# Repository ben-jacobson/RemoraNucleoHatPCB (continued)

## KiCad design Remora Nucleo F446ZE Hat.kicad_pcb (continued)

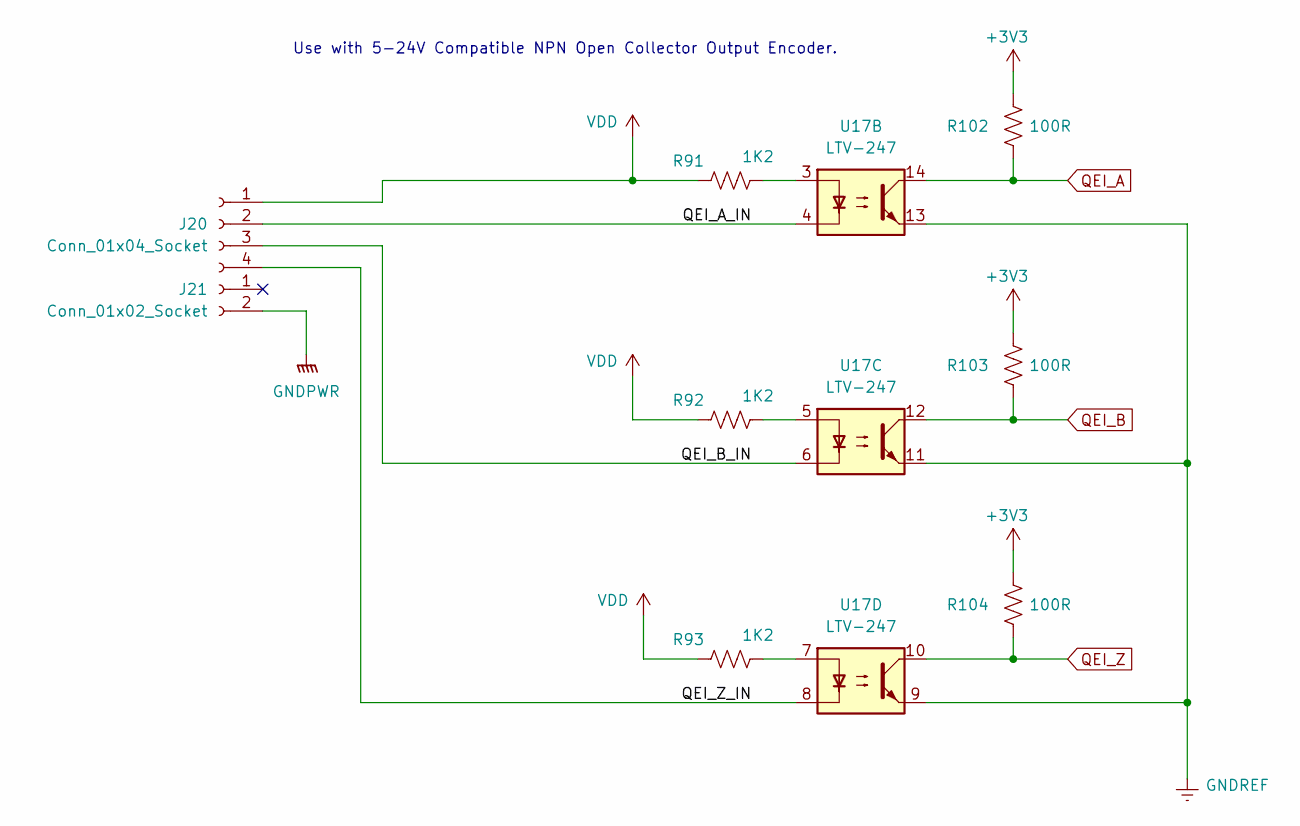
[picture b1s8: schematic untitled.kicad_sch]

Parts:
J20: Conn_01x04_Socket; 691412120004B; Digikey Part Number 732-691412120004B-ND
J21: Conn_01x02_Socket; 691412120002B; Digikey Part Number 732-691412120002B-ND
R91, R92, R93: 1K2; R_1206_3216Metric_Pad1.30x1.75mm_HandSolder; Digikey Part Number RMCF1206JT1K20CT-ND
R102, R103, R104: 100R; R_1206_3216Metric_Pad1.30x1.75mm_HandSolder
U17: LTV-247; SOP-16_4.4x10.4mm_P1.27mm; Digikey Part Number 160-2255-1-ND

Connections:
+3V3: R102.1, R103.1, R104.1; also elsewhere on the board
/Encoder Inputs/QEI_A_IN: J20.2, U17.4
/Encoder Inputs/QEI_B_IN: J20.3, U17.6
/Encoder Inputs/QEI_Z_IN: J20.4, U17.8
GNDPWR: J21.2; also elsewhere on the board
GNDREF: U17.9, U17.11, U17.13; also elsewhere on the board
unnamed: R91.1, U17.3
unnamed: R92.1, U17.5
unnamed: R93.1, U17.7
QEI_A: R102.2, U17.14; also elsewhere on the board
QEI_B: R103.2, U17.12; also elsewhere on the board
QEI_Z: R104.2, U17.10; also elsewhere on the board
VDD: J20.1, R91.2, R92.2, R93.2; also elsewhere on the board

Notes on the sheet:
Use with 5-24V Compatible NPN Open Collector Output Encoder.

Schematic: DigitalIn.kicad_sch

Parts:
R33, R34, R35, R36: 180R; R_1206_3216Metric_Pad1.30x1.75mm_HandSolder; Digikey Part Number 311-180FRCT-ND
U7: LTV-247; SOP-16_4.4x10.4mm_P1.27mm; Digikey Part Number 160-2255-1-ND

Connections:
+5VD: R33.1, R34.1, R35.1, R36.1; also elsewhere on the board
/Digital Inputs/Digital Input 4-7/INPUT4: U7.2; also elsewhere on the board
/Digital Inputs/Digital Input 4-7/INPUT5: U7.4; also elsewhere on the board
/Digital Inputs/Digital Input 4-7/INPUT6: U7.6; also elsewhere on the board
/Digital Inputs/Digital Input 4-7/INPUT7: U7.8; also elsewhere on the board
GNDREF: U7.9, U7.11, U7.13, U7.15; also elsewhere on the board
MCU_DIGITAL_IN_4: U7.16; also elsewhere on the board
MCU_DIGITAL_IN_5: U7.14; also elsewhere on the board
MCU_DIGITAL_IN_6: U7.12; also elsewhere on the board
MCU_DIGITAL_IN_7: U7.10; also elsewhere on the board
unnamed: R33.2, U7.1
unnamed: R34.2, U7.3
unnamed: R35.2, U7.5
unnamed: R36.2, U7.7

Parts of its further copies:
R41, R42, R43, R44, R45, R46, R47, R48, R49, R50, R51, R52: 180R; R_1206_3216Metric_Pad1.30x1.75mm_HandSolder; Digikey Part Number 311-180FRCT-ND
U9, U10, U11: LTV-247; SOP-16_4.4x10.4mm_P1.27mm; Digikey Part Number 160-2255-1-ND

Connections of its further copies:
+5VD: R41.1, R42.1, R43.1, R44.1, R45.1, R46.1, R47.1, R48.1, R49.1, R50.1, R51.1, R52.1; also elsewhere on the board
/Digital Inputs/Digital Input 0-3/INPUT0: U11.2; also elsewhere on the board
/Digital Inputs/Digital Input 0-3/INPUT1: U11.4; also elsewhere on the board
/Digital Inputs/Digital Input 0-3/INPUT2: U11.6; also elsewhere on the board
/Digital Inputs/Digital Input 0-3/INPUT3: U11.8; also elsewhere on the board
/Digital Inputs/Digital Input 8-11/INPUT8: U9.2; also elsewhere on the board
/Digital Inputs/Digital Input 8-11/INPUT9: U9.4; also elsewhere on the board
/Digital Inputs/Digital Input 8-11/INPUT10: U9.6; also elsewhere on the board
/Digital Inputs/Digital Input 8-11/INPUT11: U9.8; also elsewhere on the board
/Digital Inputs/Digital Input 12-15/INPUT12: U10.2; also elsewhere on the board
/Digital Inputs/Digital Input 12-15/INPUT13: U10.4; also elsewhere on the board
/Digital Inputs/Digital Input 12-15/INPUT14: U10.6; also elsewhere on the board
/Digital Inputs/Digital Input 12-15/INPUT15: U10.8; also elsewhere on the board
GNDREF: U9.9, U9.11, U9.13, U9.15, U10.9, U10.11, U10.13, U10.15, U11.9, U11.11, U11.13, U11.15; also elsewhere on the board
MCU_DIGITAL_IN_0: U11.16; also elsewhere on the board
MCU_DIGITAL_IN_1: U11.14; also elsewhere on the board
MCU_DIGITAL_IN_2: U11.12; also elsewhere on the board
MCU_DIGITAL_IN_3: U11.10; also elsewhere on the board
MCU_DIGITAL_IN_8: U9.16; also elsewhere on the board
MCU_DIGITAL_IN_9: U9.14; also elsewhere on the board
MCU_DIGITAL_IN_10: U9.12; also elsewhere on the board
MCU_DIGITAL_IN_11: U9.10; also elsewhere on the board
MCU_DIGITAL_IN_12: U10.16; also elsewhere on the board
MCU_DIGITAL_IN_13: U10.14; also elsewhere on the board
MCU_DIGITAL_IN_14: U10.12; also elsewhere on the board
MCU_DIGITAL_IN_15: U10.10; also elsewhere on the board
unnamed: R41.2, U9.1
unnamed: R42.2, U9.3
unnamed: R43.2, U9.5
unnamed: R44.2, U9.7
unnamed: R45.2, U10.1
unnamed: R46.2, U10.3
unnamed: R47.2, U10.5
unnamed: R48.2, U10.7
unnamed: R49.2, U11.1
unnamed: R50.2, U11.3
unnamed: R51.2, U11.5
unnamed: R52.2, U11.7

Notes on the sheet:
NPN Inputs

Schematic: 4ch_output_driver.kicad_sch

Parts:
F1, F2, F3, F4: PRG18BB330MB1RB; Fuse_0603_1608Metric_Pad1.05x0.95mm_HandSolder; Digikey Part Number 490-2471-1-ND
R29, R30, R31, R32: 180R; R_1206_3216Metric_Pad1.30x1.75mm_HandSolder; Digikey Part Number 311-180FRCT-ND
U6: LTV-247; SOP-16_4.4x10.4mm_P1.27mm; Digikey Part Number 160-2255-1-ND

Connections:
/Digital Outputs/4CH digital output driver 1/OUTPUT0: F1.2; also elsewhere on the board
/Digital Outputs/4CH digital output driver 1/OUTPUT1: F2.2; also elsewhere on the board
/Digital Outputs/4CH digital output driver 1/OUTPUT2: F3.2; also elsewhere on the board
/Digital Outputs/4CH digital output driver 1/OUTPUT3: F4.2; also elsewhere on the board
GNDPWR: U6.9, U6.11, U6.13, U6.15; also elsewhere on the board
GNDREF: U6.2, U6.4, U6.6, U6.8; also elsewhere on the board
MCU_DIGITAL_OUT_0: R29.1; also elsewhere on the board
MCU_DIGITAL_OUT_1: R30.1; also elsewhere on the board
MCU_DIGITAL_OUT_2: R31.1; also elsewhere on the board
MCU_DIGITAL_OUT_3: R32.1; also elsewhere on the board
unnamed: F1.1, U6.16
unnamed: F2.1, U6.14
unnamed: F3.1, U6.12
unnamed: F4.1, U6.10
unnamed: R29.2, U6.1
unnamed: R30.2, U6.3
unnamed: R31.2, U6.5
unnamed: R32.2, U6.7

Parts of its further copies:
F5, F6, F7, F8: PRG18BB330MB1RB; Fuse_0603_1608Metric_Pad1.05x0.95mm_HandSolder; Digikey Part Number 490-2471-1-ND
R37, R38, R39, R40: 180R; R_1206_3216Metric_Pad1.30x1.75mm_HandSolder; Digikey Part Number 311-180FRCT-ND
U8: LTV-247; SOP-16_4.4x10.4mm_P1.27mm; Digikey Part Number 160-2255-1-ND

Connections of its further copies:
/Digital Outputs/4CH digital output driver 2/OUTPUT4: F5.2; also elsewhere on the board
/Digital Outputs/4CH digital output driver 2/OUTPUT5: F6.2; also elsewhere on the board
/Digital Outputs/4CH digital output driver 2/OUTPUT6: F7.2; also elsewhere on the board
/Digital Outputs/4CH digital output driver 2/OUTPUT7: F8.2; also elsewhere on the board
GNDPWR: U8.9, U8.11, U8.13, U8.15; also elsewhere on the board
GNDREF: U8.2, U8.4, U8.6, U8.8; also elsewhere on the board
MCU_DIGITAL_OUT_4: R37.1; also elsewhere on the board
MCU_DIGITAL_OUT_5: R38.1; also elsewhere on the board
MCU_DIGITAL_OUT_6: R39.1; also elsewhere on the board
MCU_DIGITAL_OUT_7: R40.1; also elsewhere on the board
unnamed: F5.1, U8.16
unnamed: F6.1, U8.14
unnamed: F7.1, U8.12
unnamed: F8.1, U8.10
unnamed: R37.2, U8.1
unnamed: R38.2, U8.3
unnamed: R39.2, U8.5
unnamed: R40.2, U8.7

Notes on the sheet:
NPN Outputs

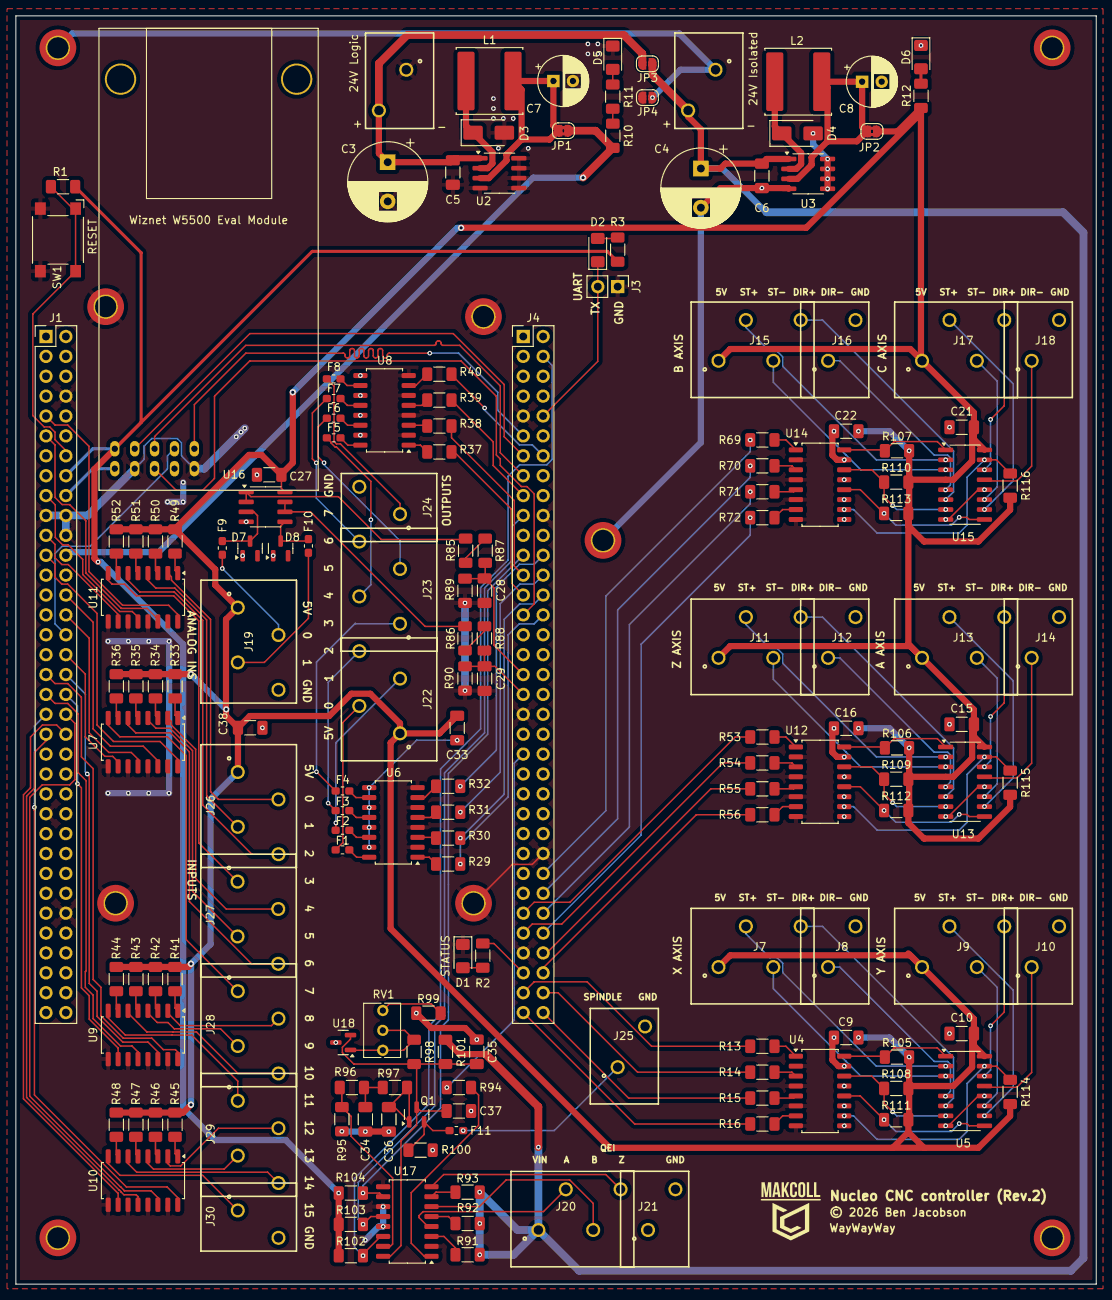
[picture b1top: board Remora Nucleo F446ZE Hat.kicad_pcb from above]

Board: 2 copper layers, 138.0 x 162.0 mm, 179 parts (0 on the bottom side), 194 nets.

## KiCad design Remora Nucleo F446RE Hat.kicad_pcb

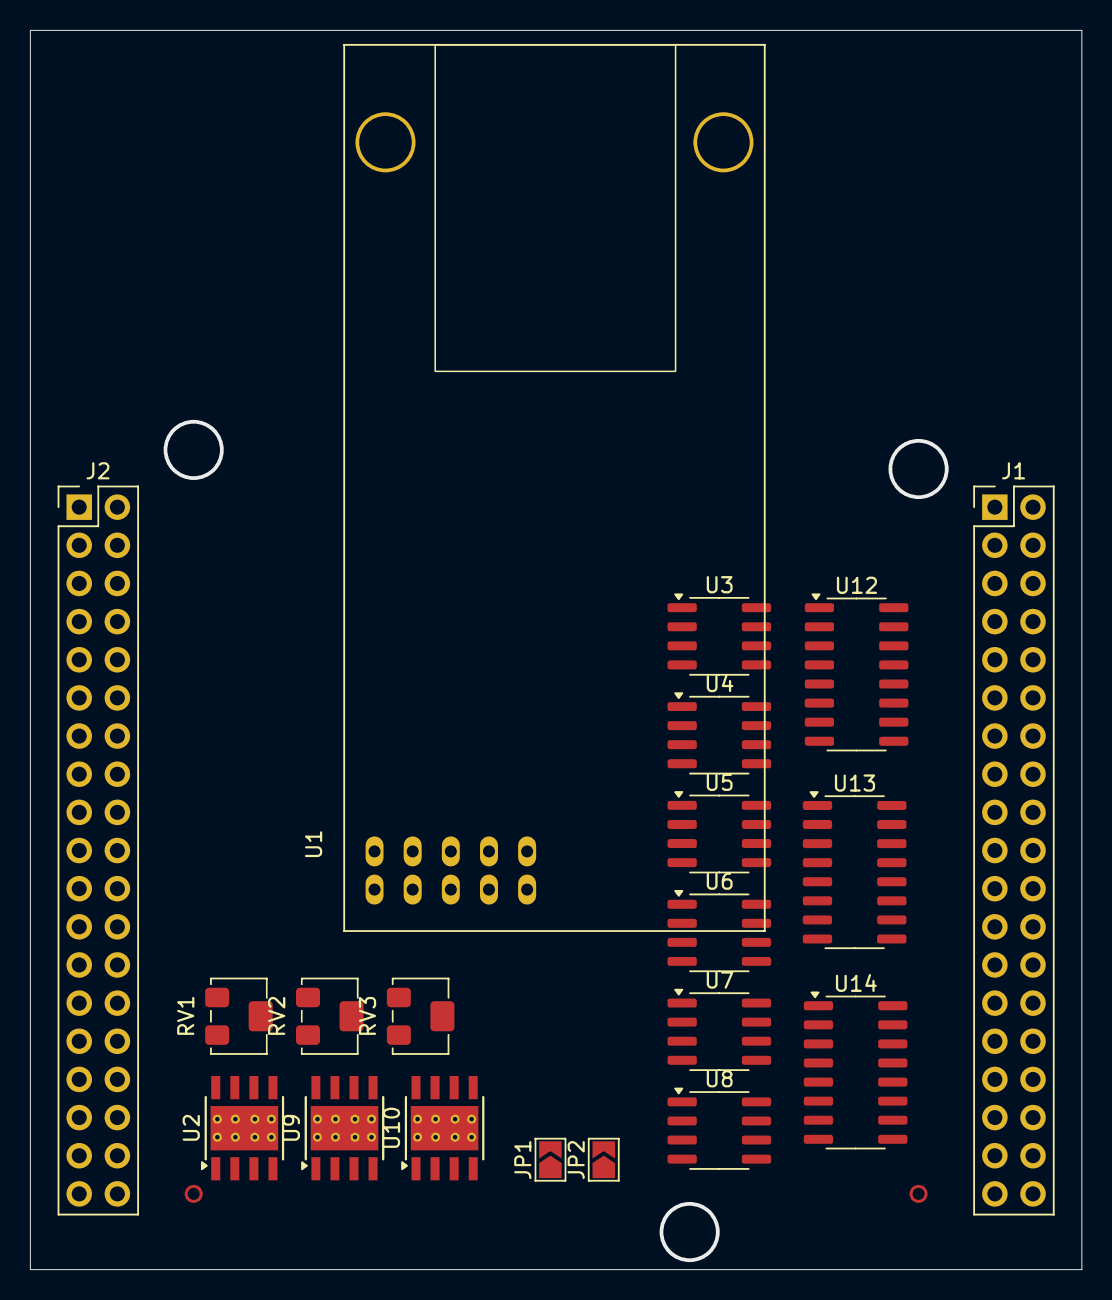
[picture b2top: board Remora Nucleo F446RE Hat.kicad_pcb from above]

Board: 2 copper layers, 70.0 x 82.5 mm, 20 parts (0 on the bottom side), 28 nets, no tracks yet.

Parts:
J1: NucleoF446RE CN10 Header; PinHeader_2x19_P2.54mm_Vertical
J2: NucleoF446RE CN7 Header; PinHeader_2x19_P2.54mm_Vertical
JP1: EXT_5V_SUPPLY_JMP; SolderJumper-2_P1.3mm_Open_TrianglePad1.0x1.5mm
JP2: EXT_5V_GND_JMP; SolderJumper-2_P1.3mm_Open_TrianglePad1.0x1.5mm
RV1, RV3: 50R trimpot; Potentiometer_Bourns_3224W_Vertical
RV2: 500R trimpot; Potentiometer_Bourns_3224W_Vertical
U1: W5500EvalModule
U2, U9, U10: TPS5430DDAR; TI_SO-PowerPAD-8_ThermalVias
U3, U4, U5, U6, U7, U8: ADuM1201AR; SOIC-8_3.9x4.9mm_P1.27mm
U12, U13, U14: HT26LS31ARZ; SOIC-16_3.9x9.9mm_P1.27mm

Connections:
5V_GND: JP2.1 (A), U3.5 (GND2), U4.5 (GND2), U5.5 (GND2), U6.5 (GND2), U7.5 (GND2), U8.5 (GND2), U12.8 (GND), U12.12 (~G), U13.8 (GND), U13.12 (~G), U14.8 (GND), U14.12 (~G)
+3V3: U1.5 (3V3), U3.1 (VDD1), U4.1 (VDD1), U5.1 (VDD1), U6.1 (VDD1), U7.1 (VDD1), U8.1 (VDD1)
+5V: JP1.2 (B), U1.6 (5V)
+5VD: JP1.1 (A), U3.8 (VDD2), U4.8 (VDD2), U5.8 (VDD2), U6.8 (VDD2), U7.8 (VDD2), U8.8 (VDD2), U12.4 (G), U12.16 (VDD), U13.4 (G), U13.16 (VDD), U14.4 (G), U14.16 (VDD)
+12V: U9.7 (VIN), U10.7 (VIN)
GNDREF: J1.9, J1.20, J2.8, J2.19, J2.20, J2.22, JP2.2 (B), U1.7 (GND), U1.10 (GND), U2.6 (GND), U2.9 (GNDPAD), U3.4 (GND1), U4.4 (GND1), U5.4 (GND1), U6.4 (GND1), U7.4 (GND1), U8.4 (GND1), U9.6 (GND), U9.9 (GNDPAD), U10.6 (GND), U10.9 (GNDPAD)
unnamed: RV3.2, RV3.3
unnamed: RV1.2, RV1.3
unnamed: RV2.2, RV2.3
unnamed: U3.2 (VOA), U12.1 (1A)
unnamed: U3.6 (VOB), U12.7 (2A)
unnamed: U4.2 (VOA), U12.9 (3A)
unnamed: U4.6 (VOB), U12.15 (4A)
unnamed: U5.2 (VOA), U13.1 (1A)
unnamed: U5.6 (VOB), U13.7 (2A)
unnamed: U6.2 (VOA), U13.9 (3A)
unnamed: U6.6 (VOB), U13.15 (4A)
unnamed: U7.2 (VOA), U14.1 (1A)
unnamed: U7.6 (VOB), U14.7 (2A)
unnamed: U8.2 (VOA), U14.9 (3A)
unnamed: U8.6 (VOB), U14.15 (4A)
SPI1_CLK: J1.31, U1.1 (SLCK)
SPI1_MISO: J1.27, U1.4 (MISO)
SPI1_MOSI: J1.29, U1.3 (MOSI)
VSENSE: RV1.1, RV2.1, RV3.1, U2.4 (VSENSE), U9.4 (VSENSE), U10.4 (VSENSE)
WIZ_CS: J2.17, U1.2 (SCS)
WIZ_INT: J1.21, U1.9 (INT)
WIZ_RST: J2.37, U1.8 (RST)

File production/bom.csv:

Designator,Footprint,Quantity,Value,LCSC Part #
J1,PinHeader_2x19_P2.54mm_Vertical,1,NucleoF446RE CN10 Header,
J2,PinHeader_2x19_P2.54mm_Vertical,1,NucleoF446RE CN7 Header,
JP1,SolderJumper-2_P1.3mm_Open_TrianglePad1.0x1.5mm,1,EXT_5V_SUPPLY_JMP,
JP2,SolderJumper-2_P1.3mm_Open_TrianglePad1.0x1.5mm,1,EXT_5V_GND_JMP,
"RV1, RV3",Potentiometer_Bourns_3224W_Vertical,2,50R trimpot,
RV2,Potentiometer_Bourns_3224W_Vertical,1,500R trimpot,
U1,W5500EvalModule,1,~,
"U10, U2, U9",TI_SO-PowerPAD-8_ThermalVias,3,TPS5430DDAR,
"U12, U13, U14",SOIC-16_3.9x9.9mm_P1.27mm,3,HT26LS31ARZ,
"U3, U4, U5, U6, U7, U8",SOIC-8_3.9x4.9mm_P1.27mm,6,ADuM1201AR,

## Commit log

2025-06-02 Update README.md
    typo!
2025-06-02 Initial details in README.md
2025-06-02 Modified gitignore for better handling of kicad files
2025-06-02 Initial tidy of untracked files
2025-06-02 missed backups
2025-06-02 more files...
2025-06-02 another unused lock file, that should be it for now
2025-06-04 remapping IO pins around unavailable IO on board. Steppers are still in progress
2025-06-04 Moved UART to use STLink default comms port, frees up 2x GPIO
2025-06-04 Bug no longer reproducible with ZDir. excel mapping is now reflective of what works in software
2025-06-04 updates to some testing, all GPIO and stepper pins now work. Yet to test ABC axis as I don't have any example GCode for it. will have to trust that 5 axis works for now
2025-06-15 Changed board spec from Nucleo F446RE to F446ZE Altered readme to suit it and moved the Todos over.
2025-06-15 Put in disclaimer in README and removed deprecated production file
2025-06-15 tweaked board edge cuts, mouting hole positions and pin headers to match mechanical drawing. Yet to validate with physical hardware
2025-06-16 rewired the UART to use virtual comm port
2025-06-16 changes some unecessary global labels to local. Added a heirarchical sheet for output driver and basic numbering. Sink logic not yet set for O/Ps, but placeholder for now
2025-06-16 updates to readme
2025-06-16 added reset button, programmable user button, user LED and updates to todos
2025-06-17 fixed error in placement of usr_button and pull down config
2025-06-17 redrew stepper drivers as duplicatable heirarchical sheets, moved jumpers into power managemente sheet, moved LEDs and user buttons into own sheet to save space. Fixed a few random labelling issues.
2025-06-17 fixes to readme, compiled a few notes and fleshed out some of the todos
2025-06-17 Found a bug in the circuit, using the wrong isolated tranceivers, fixed.
2025-06-18 Completed design for digital outputs, tidied into own sheets and bussing for scalability
2025-06-18 updates to todos
2025-06-20 tidy of some sheets. Added 0-10V DAC, but untested - only some basic validation on simulator for now
2025-06-21 Simplified spindle DAC. Performs better in simulator.
2025-06-21 buffered output on spindle DAC, tweak to gain structure and update to readme
2025-06-23 Added some background in readme
2025-06-24 digital inputs section
2025-06-26 Deleted stale test production files. Fixed up a bug with power isolation. Created some footprints for wire to board connectors although ran out of time to fix a bug where they do no lock in. Fixes to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
2025-07-01 restructured power supplies to enable Spindle DAC to be isolated. We now have the option of supplying two 24V inputs, one to power the nucleo and everything logic side and the other to power peripher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
2025-07-04 Fixes to screw terminal footprints, updated BOM and included in project folder
2025-07-13 Added preview schematics
2025-09-29 saving work to move to other pc
2025-09-29 moved SPI1_CS to new place. Added MicroSD card and SDIO interface to schematic
2025-09-30 Fixes to bypass caps in micro SD + imported and assigned footprint file
2025-10-01 Fixed bug with lack of pin header for CN11 and CN12. Addeded RPI header and aligned it, assigned some safe footprints
2025-10-02 corrected hole spacing for Nucleo board. Double checked some of the standoff spacing and made some correction to pin header insulation heights and standoff heights too.
2025-10-05 updates to read me, marked V1 parts inactive and made start on board layout for initial test board. fixes to BOM to suit
2025-10-07 Dropped number of IO on design to make more room. Created the new footprints to suit them, updates to BOM and ran some traces on the PCB.
2025-10-11 New optocoupler part choice, removed digikey BOM as have started inputting them into symbol fields. Re-enabled all disabled parts for now and will re-design power supplies soon.
2025-10-11 fix to annoying additional symbol fields displaying when we didn't want them to.
2025-10-15 BOM consolidation for various resistors. Moved BOM into symbol libraries and updated supplimentary BOM. Switched IO optical isolation circuitry to a more cost effective part.
2025-10-15 Renumbered IO to start at 0 to match firmware
2025-10-15 Corrections to digital input pins
2025-10-17 more BOM consolidation. Switched out IO for vertical toolless wire to board terminals and added footprints. Put new isolated ground plane on board.
2025-10-18 Swapped out stepper isolators to use same as others. further BOM consolidation. Fixed bug with incorrect differential driver footprint.
2025-10-22 Built up stepper driver circuit on breadboard and tested up to 100khz, made some tweaks and happy to report this part of the design is now validated
2025-10-22 updates to readme to reflect new specs
2025-11-01 Tweaks to stepper driver circuitry after some validation on breadboard. IO now fully validated
2025-11-05 New PSU schematics
2025-11-21 New PSU designs + footprints assigned. Changes to board shape to make room for new components. BOM consolidation of supplimentary file
2025-11-23 Layout work for PSUs
2025-11-25 Changes to input after testing with some optical sensors
2025-12-03 Added Analog inputs, updates to readme re powering board from external supply
2025-12-22 Finalised Spindle DAC, working as expected
2026-02-06 Added high speed encoder input circuitry. General tidy and updates to readme
2026-02-16 Testing multi channel layout, test layout for stepper drivers
2026-03-03 Layout for stepper drivers and digital inputs
2026-03-22 Switched terminal footprints over to a finer pitch. Corrected an issue with component reference values preventing proper use of multi channel rule areas. Component references for 4 channel optos are 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
2026-03-22 Added 3d Models for new terminal connectors for easy board verification before committing to build
2026-03-29 Redo of layout to use smaller terminals, applied to steppers and inputs and laid out outputs too
2026-03-29 Quick QEI addin. Fixed clearance issues for mounting screw
2026-03-30 initial analog input layout
2026-03-31 Spindle out layout, rejigged QEI and moved it, minor tweak to PSU positioning
2026-04-02 indiscriminate routing, placement experiments, etc
2026-04-03 Initial tracing done, prior to ERC
2026-04-03 Finished traces and DRC passes the critical tests
2026-04-04 tweaks, verified mechanical fitment, gerber files are ready for production
2026-04-04 Caught some errors with spacing of jumpers, did some BOM consolidation and included BOM. Updates to Gerbers to reflect new changes.
2026-04-04 Should not include zip files in this repo, almost committed an incorrect file. Delete now
2026-04-05 About to order PCB, checked pinouts on ordered parts, reannotated and one last DRC before exporting final gerbers
2026-04-06 Some file changes and output new gerbers + BOM and centroid file for PCBWay Order
2026-04-28 Fixed error in opamp part number
2026-05-20 Fixed found issue with oversized regulator input cap
2026-06-02 Updates to readme, working through testing and validation of board. Corrected pull ups on differential stepper outputs. Slight tweak to encoder. Tidied up some traces. Somehow lost the mounting holes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
2026-06-03 restored mounting holes and redid as proper pads, tidied up unused traces and pads. Wired in additional encoder pullups
2026-06-03 fixed incorrect labels
